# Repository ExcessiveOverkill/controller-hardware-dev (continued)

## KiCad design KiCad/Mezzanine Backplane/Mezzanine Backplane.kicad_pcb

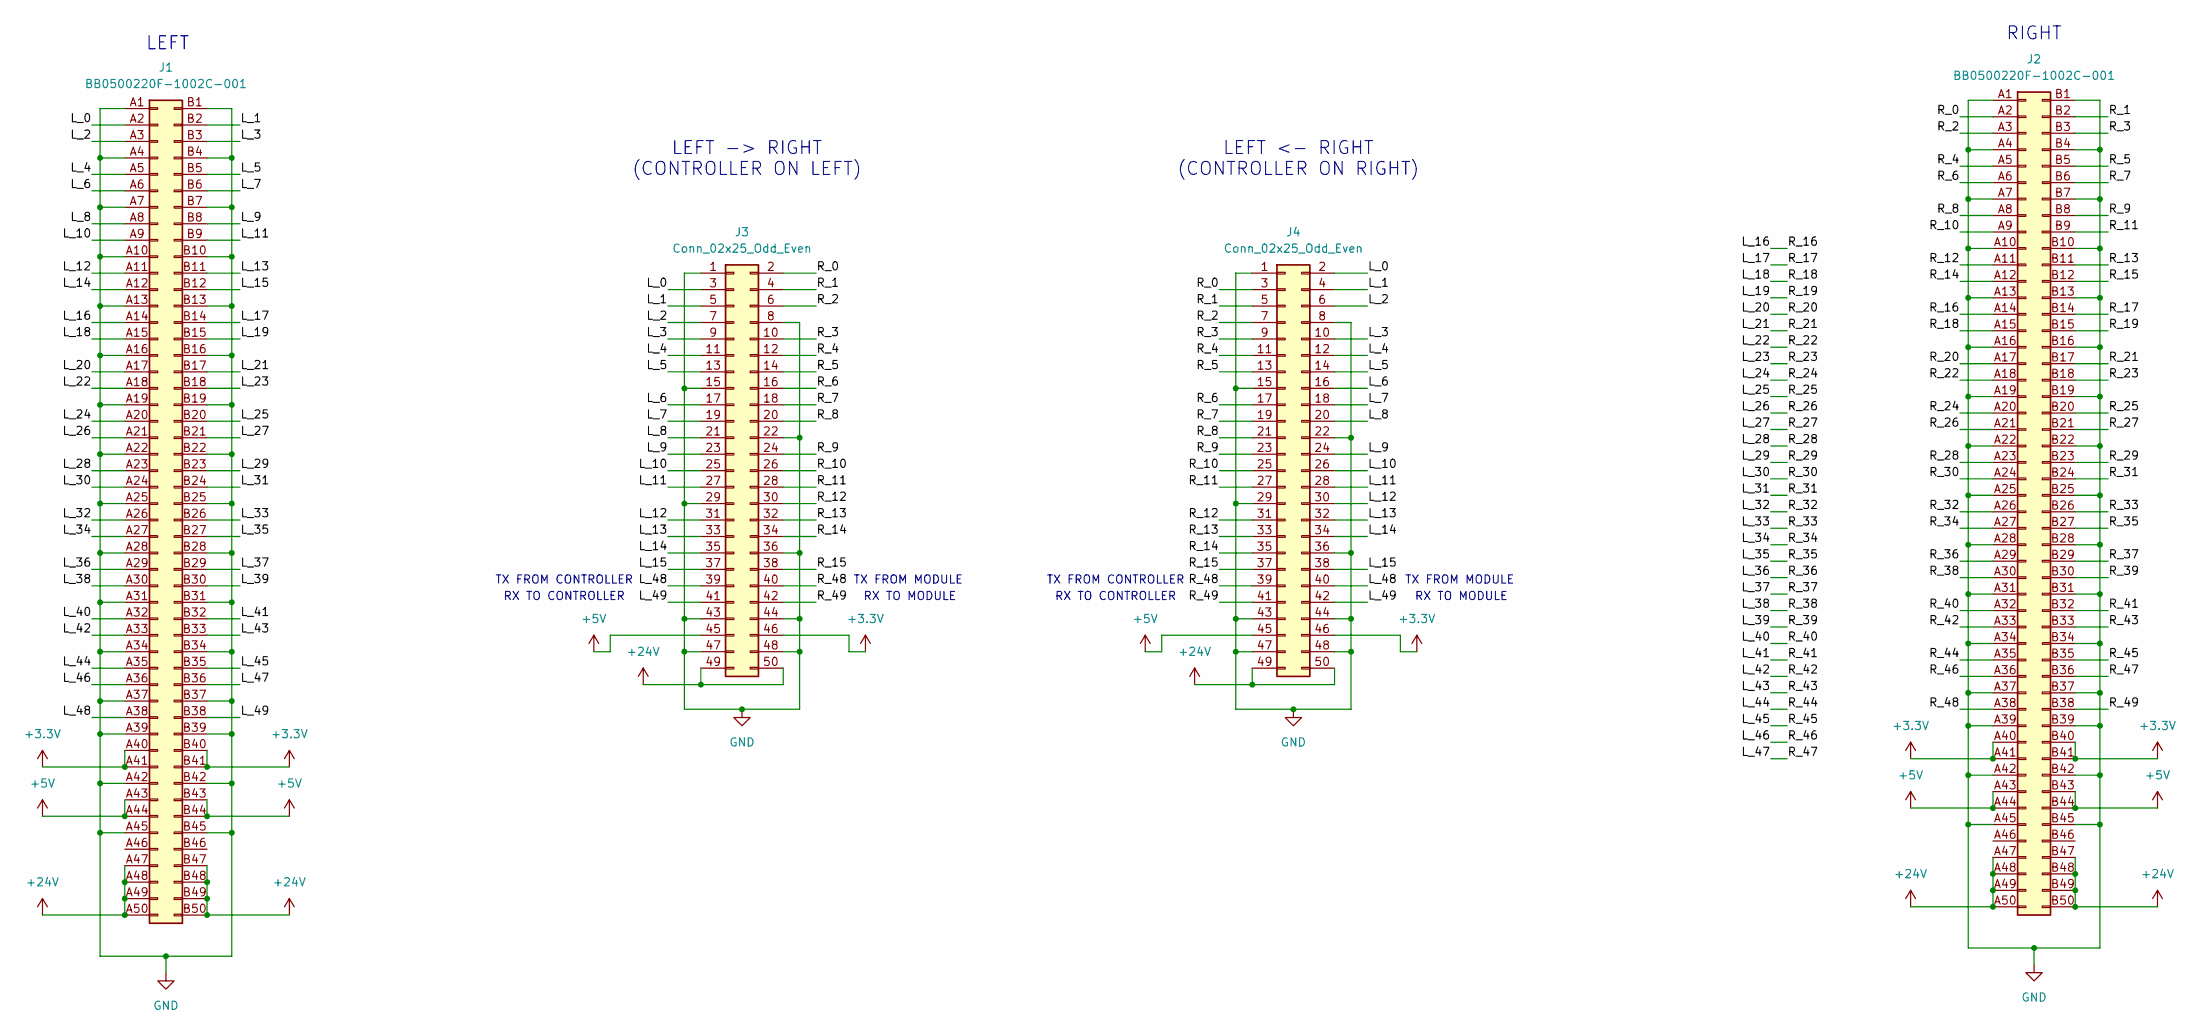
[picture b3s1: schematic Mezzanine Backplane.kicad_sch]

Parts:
J1, J2: BB0500220F-1002C-001; Part Number BB0500220F-1002C-001; LCSC# C42421167
J3, J4: Conn_02x25_Odd_Even; PinSocket_2x25_P2.00mm_Vertical_SMD; Part Number HC-PM200-4.3H-2x25PS; LCSC# C42163108

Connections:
+3.3V: J1.A40, J1.A41, J1.B40, J1.B41, J2.A40, J2.A41, J2.B40, J2.B41, J3.46, J4.46
+5V: J1.A43, J1.A44, J1.B43, J1.B44, J2.A43, J2.A44, J2.B43, J2.B44, J3.45, J4.45
+24V: J1.A47, J1.A48, J1.A49, J1.A50, J1.B47, J1.B48, J1.B49, J1.B50, J2.A47, J2.A48, J2.A49, J2.A50, J2.B47, J2.B48, J2.B49, J2.B50, J3.49, J3.50, J4.49, J4.50
/L_0: J1.A2, J3.3, J4.2
/L_1: J1.B2, J3.5, J4.4
/L_2: J1.A3, J3.7, J4.6
/L_3: J1.B3, J3.9, J4.10
/L_4: J1.A5, J3.11, J4.12
/L_5: J1.B5, J3.13, J4.14
/L_6: J1.A6, J3.17, J4.16
/L_7: J1.B6, J3.19, J4.18
/L_8: J1.A8, J3.21, J4.20
/L_9: J1.B8, J3.23, J4.24
/L_10: J1.A9, J3.25, J4.26
/L_11: J1.B9, J3.27, J4.28
/L_12: J1.A11, J3.31, J4.30
/L_13: J1.B11, J3.33, J4.32
/L_14: J1.A12, J3.35, J4.34
/L_15: J1.B12, J3.37, J4.38
/L_16: J1.A14, J2.A14
/L_17: J1.B14, J2.B14
/L_18: J1.A15, J2.A15
/L_19: J1.B15, J2.B15
/L_20: J1.A17, J2.A17
/L_21: J1.B17, J2.B17
/L_22: J1.A18, J2.A18
/L_23: J1.B18, J2.B18
/L_24: J1.A20, J2.A20
/L_25: J1.B20, J2.B20
/L_26: J1.A21, J2.A21
/L_27: J1.B21, J2.B21
/L_28: J1.A23, J2.A23
/L_29: J1.B23, J2.B23
/L_30: J1.A24, J2.A24
/L_31: J1.B24, J2.B24
/L_32: J1.A26, J2.A26
/L_33: J1.B26, J2.B26
/L_34: J1.A27, J2.A27
/L_35: J1.B27, J2.B27
/L_36: J1.A29, J2.A29
/L_37: J1.B29, J2.B29
/L_38: J1.A30, J2.A30
/L_39: J1.B30, J2.B30
/L_40: J1.A32, J2.A32
/L_41: J1.B32, J2.B32
/L_42: J1.A33, J2.A33
/L_43: J1.B33, J2.B33
/L_44: J1.A35, J2.A35
/L_45: J1.B35, J2.B35
/L_46: J1.A36, J2.A36
/L_47: J1.B36, J2.B36
/L_48: J1.A38, J3.39, J4.40
/L_49: J1.B38, J3.41, J4.42
/R_0: J2.A2, J3.2, J4.3
/R_1: J2.B2, J3.4, J4.5
/R_2: J2.A3, J3.6, J4.7
/R_3: J2.B3, J3.10, J4.9
/R_4: J2.A5, J3.12, J4.11
/R_5: J2.B5, J3.14, J4.13
/R_6: J2.A6, J3.16, J4.17
/R_7: J2.B6, J3.18, J4.19
/R_8: J2.A8, J3.20, J4.21
/R_9: J2.B8, J3.24, J4.23
/R_10: J2.A9, J3.26, J4.25
/R_11: J2.B9, J3.28, J4.27
/R_12: J2.A11, J3.30, J4.31
/R_13: J2.B11, J3.32, J4.33
/R_14: J2.A12, J3.34, J4.35
/R_15: J2.B12, J3.38, J4.37
/R_48: J2.A38, J3.40, J4.39
/R_49: J2.B38, J3.42, J4.41
GND: J1.A1, J1.A4, J1.A7, J1.A10, J1.A13, J1.A16, J1.A19, J1.A22, J1.A25, J1.A28, J1.A31, J1.A34, J1.A37, J1.A39, J1.A42, J1.A45, J1.B1, J1.B4, J1.B7, J1.B10, J1.B13, J1.B16, J1.B19, J1.B22, J1.B25, J1.B28, J1.B31, J1.B34, J1.B37, J1.B39, J1.B42, J1.B45, J2.A1, J2.A4, J2.A7, J2.A10, J2.A13, J2.A16, J2.A19, J2.A22, J2.A25, J2.A28, J2.A31, J2.A34, J2.A37, J2.A39, J2.A42, J2.A45, J2.B1, J2.B4, J2.B7, J2.B10, J2.B13, J2.B16, J2.B19, J2.B22, J2.B25, J2.B28, J2.B31, J2.B34, J2.B37, J2.B39, J2.B42, J2.B45, J3.1, J3.8, J3.15, J3.22, J3.29, J3.36, J3.43, J3.44, J3.47, J3.48, J4.1, J4.8, J4.15, J4.22, J4.29, J4.36, J4.43, J4.44, J4.47, J4.48

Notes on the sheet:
RX TO MODULE
TX FROM MODULE
RIGHT
LEFT
LEFT <- RIGHT (CONTROLLER ON RIGHT)
RX TO CONTROLLER
TX FROM CONTROLLER
LEFT -> RIGHT (CONTROLLER ON LEFT)

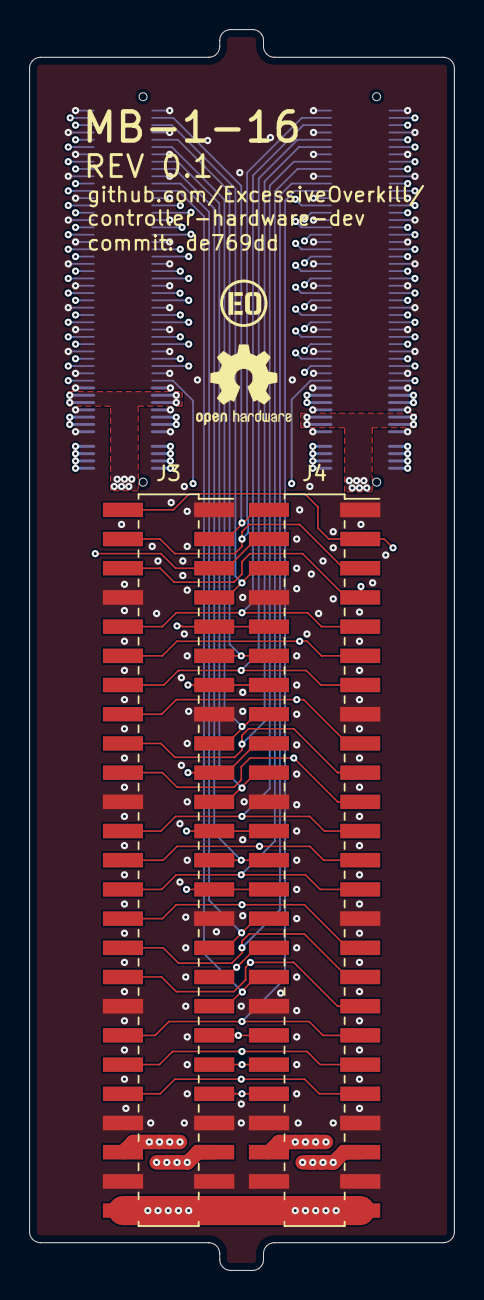
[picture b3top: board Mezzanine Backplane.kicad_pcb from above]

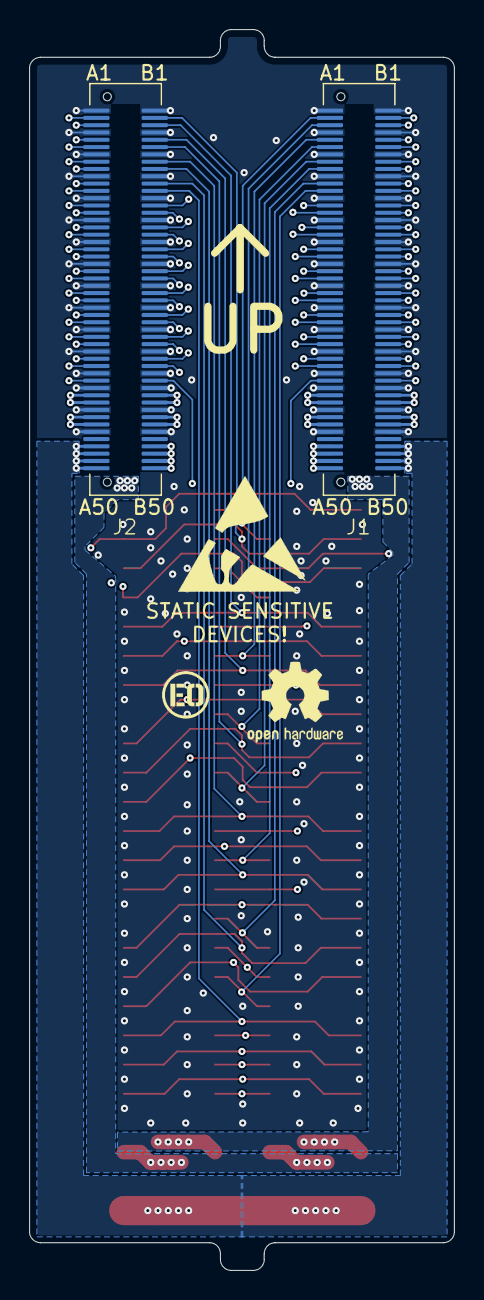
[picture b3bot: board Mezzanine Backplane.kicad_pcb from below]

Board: 4 copper layers, 29.1 x 85.0 mm, 4 parts (2 on the bottom side), 72 nets.

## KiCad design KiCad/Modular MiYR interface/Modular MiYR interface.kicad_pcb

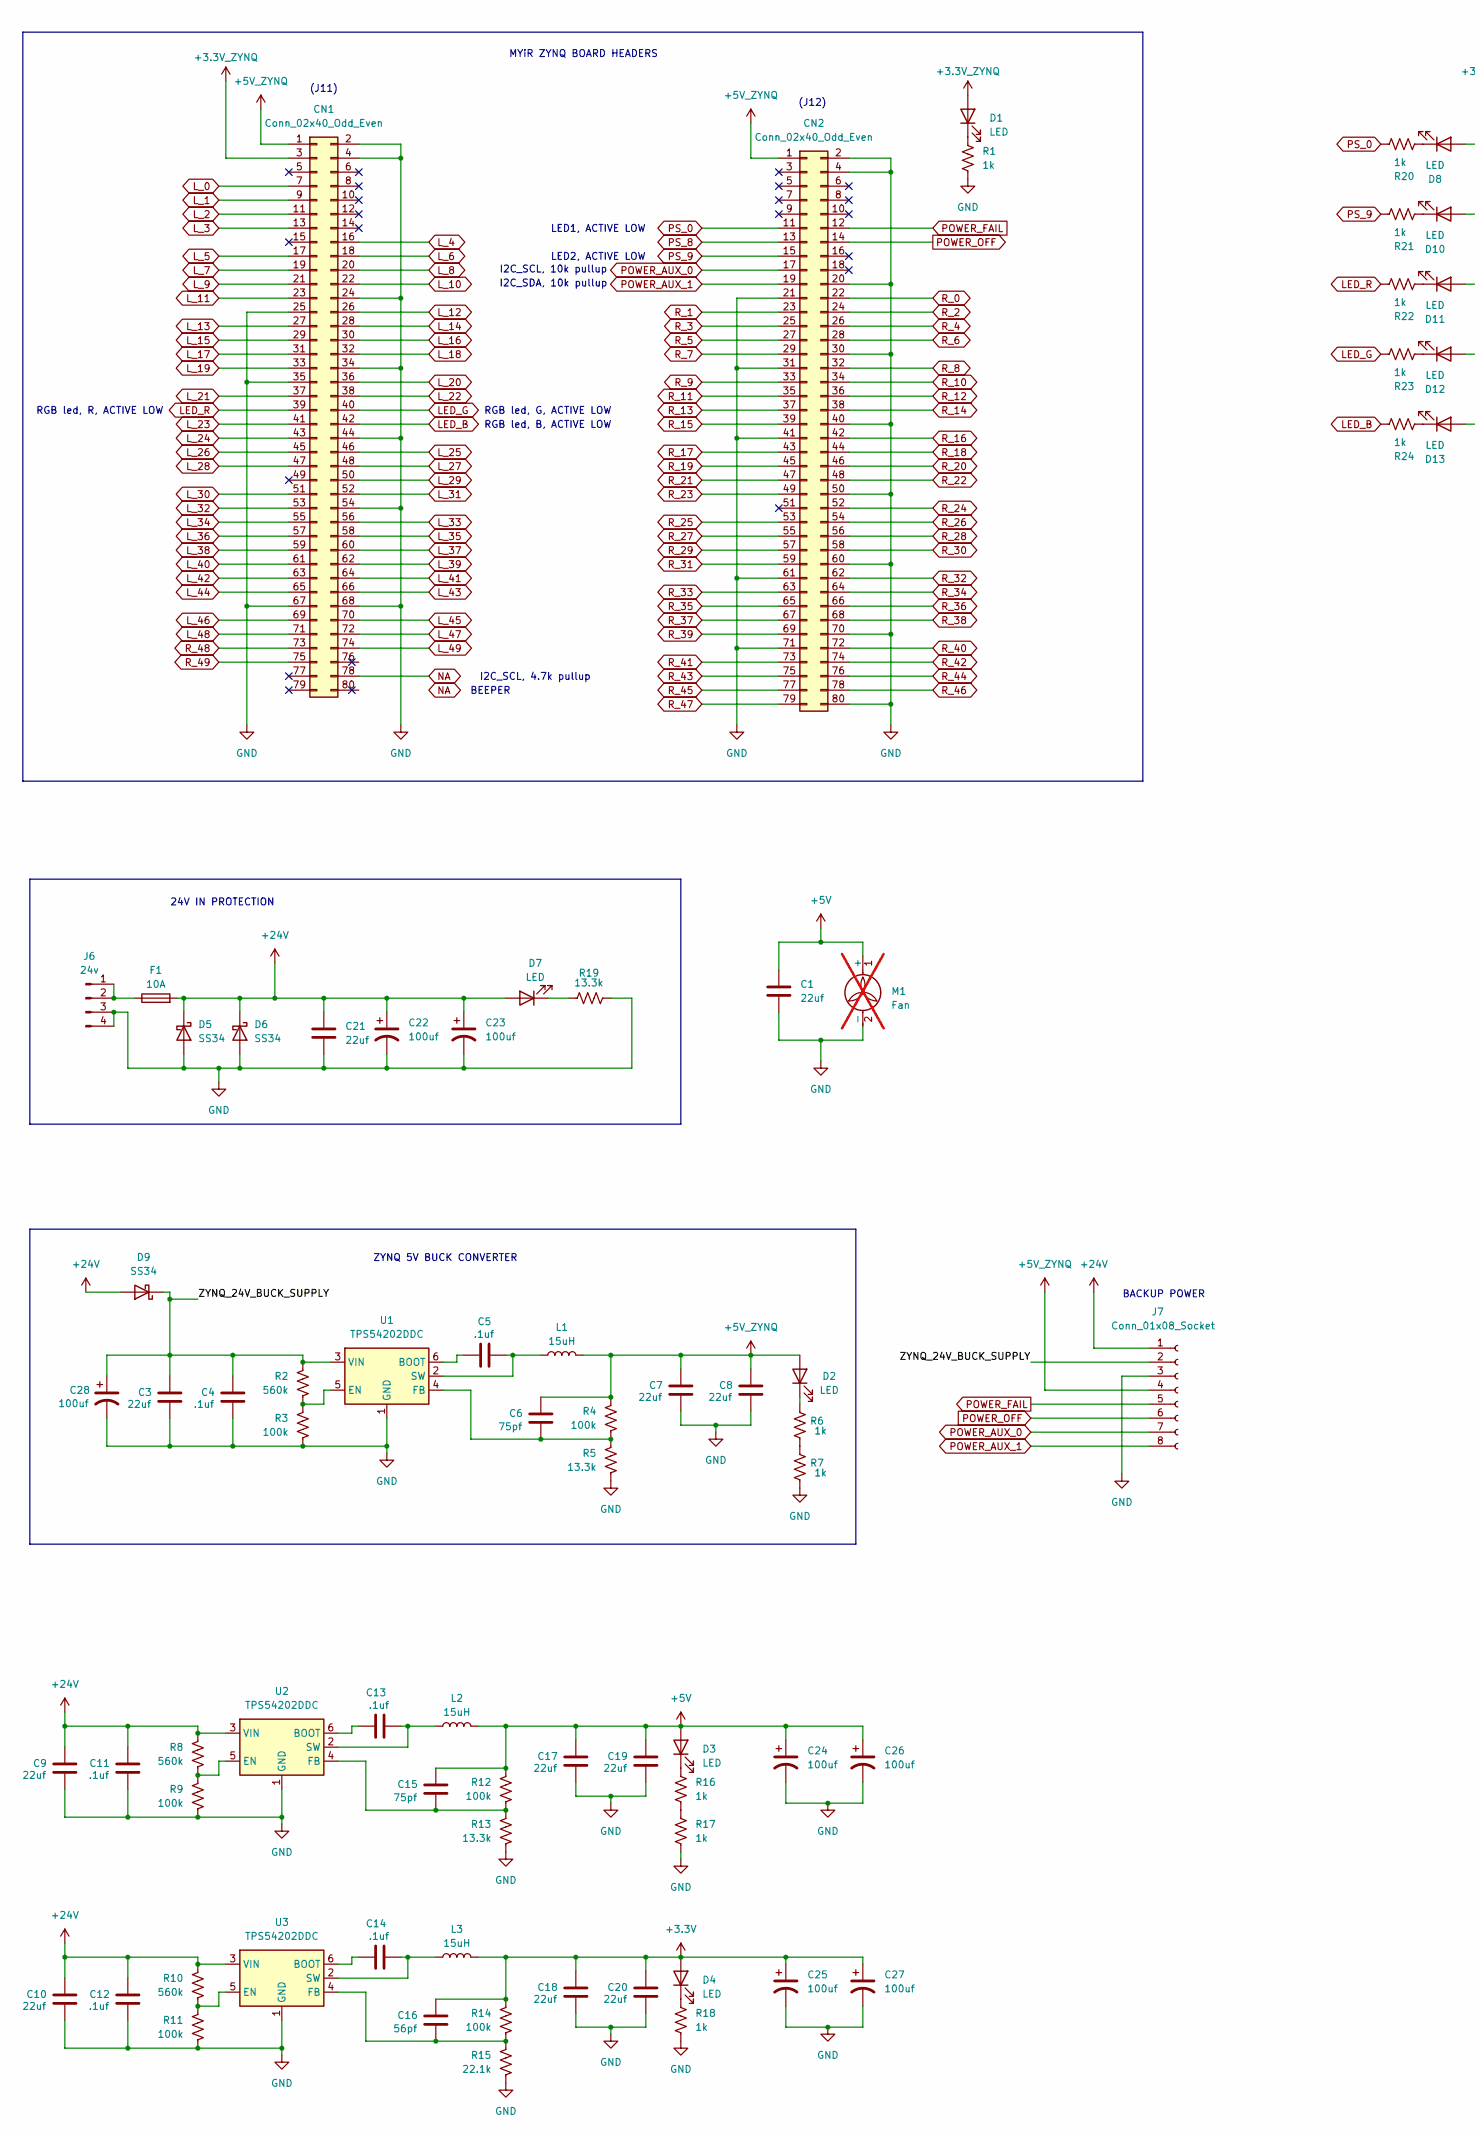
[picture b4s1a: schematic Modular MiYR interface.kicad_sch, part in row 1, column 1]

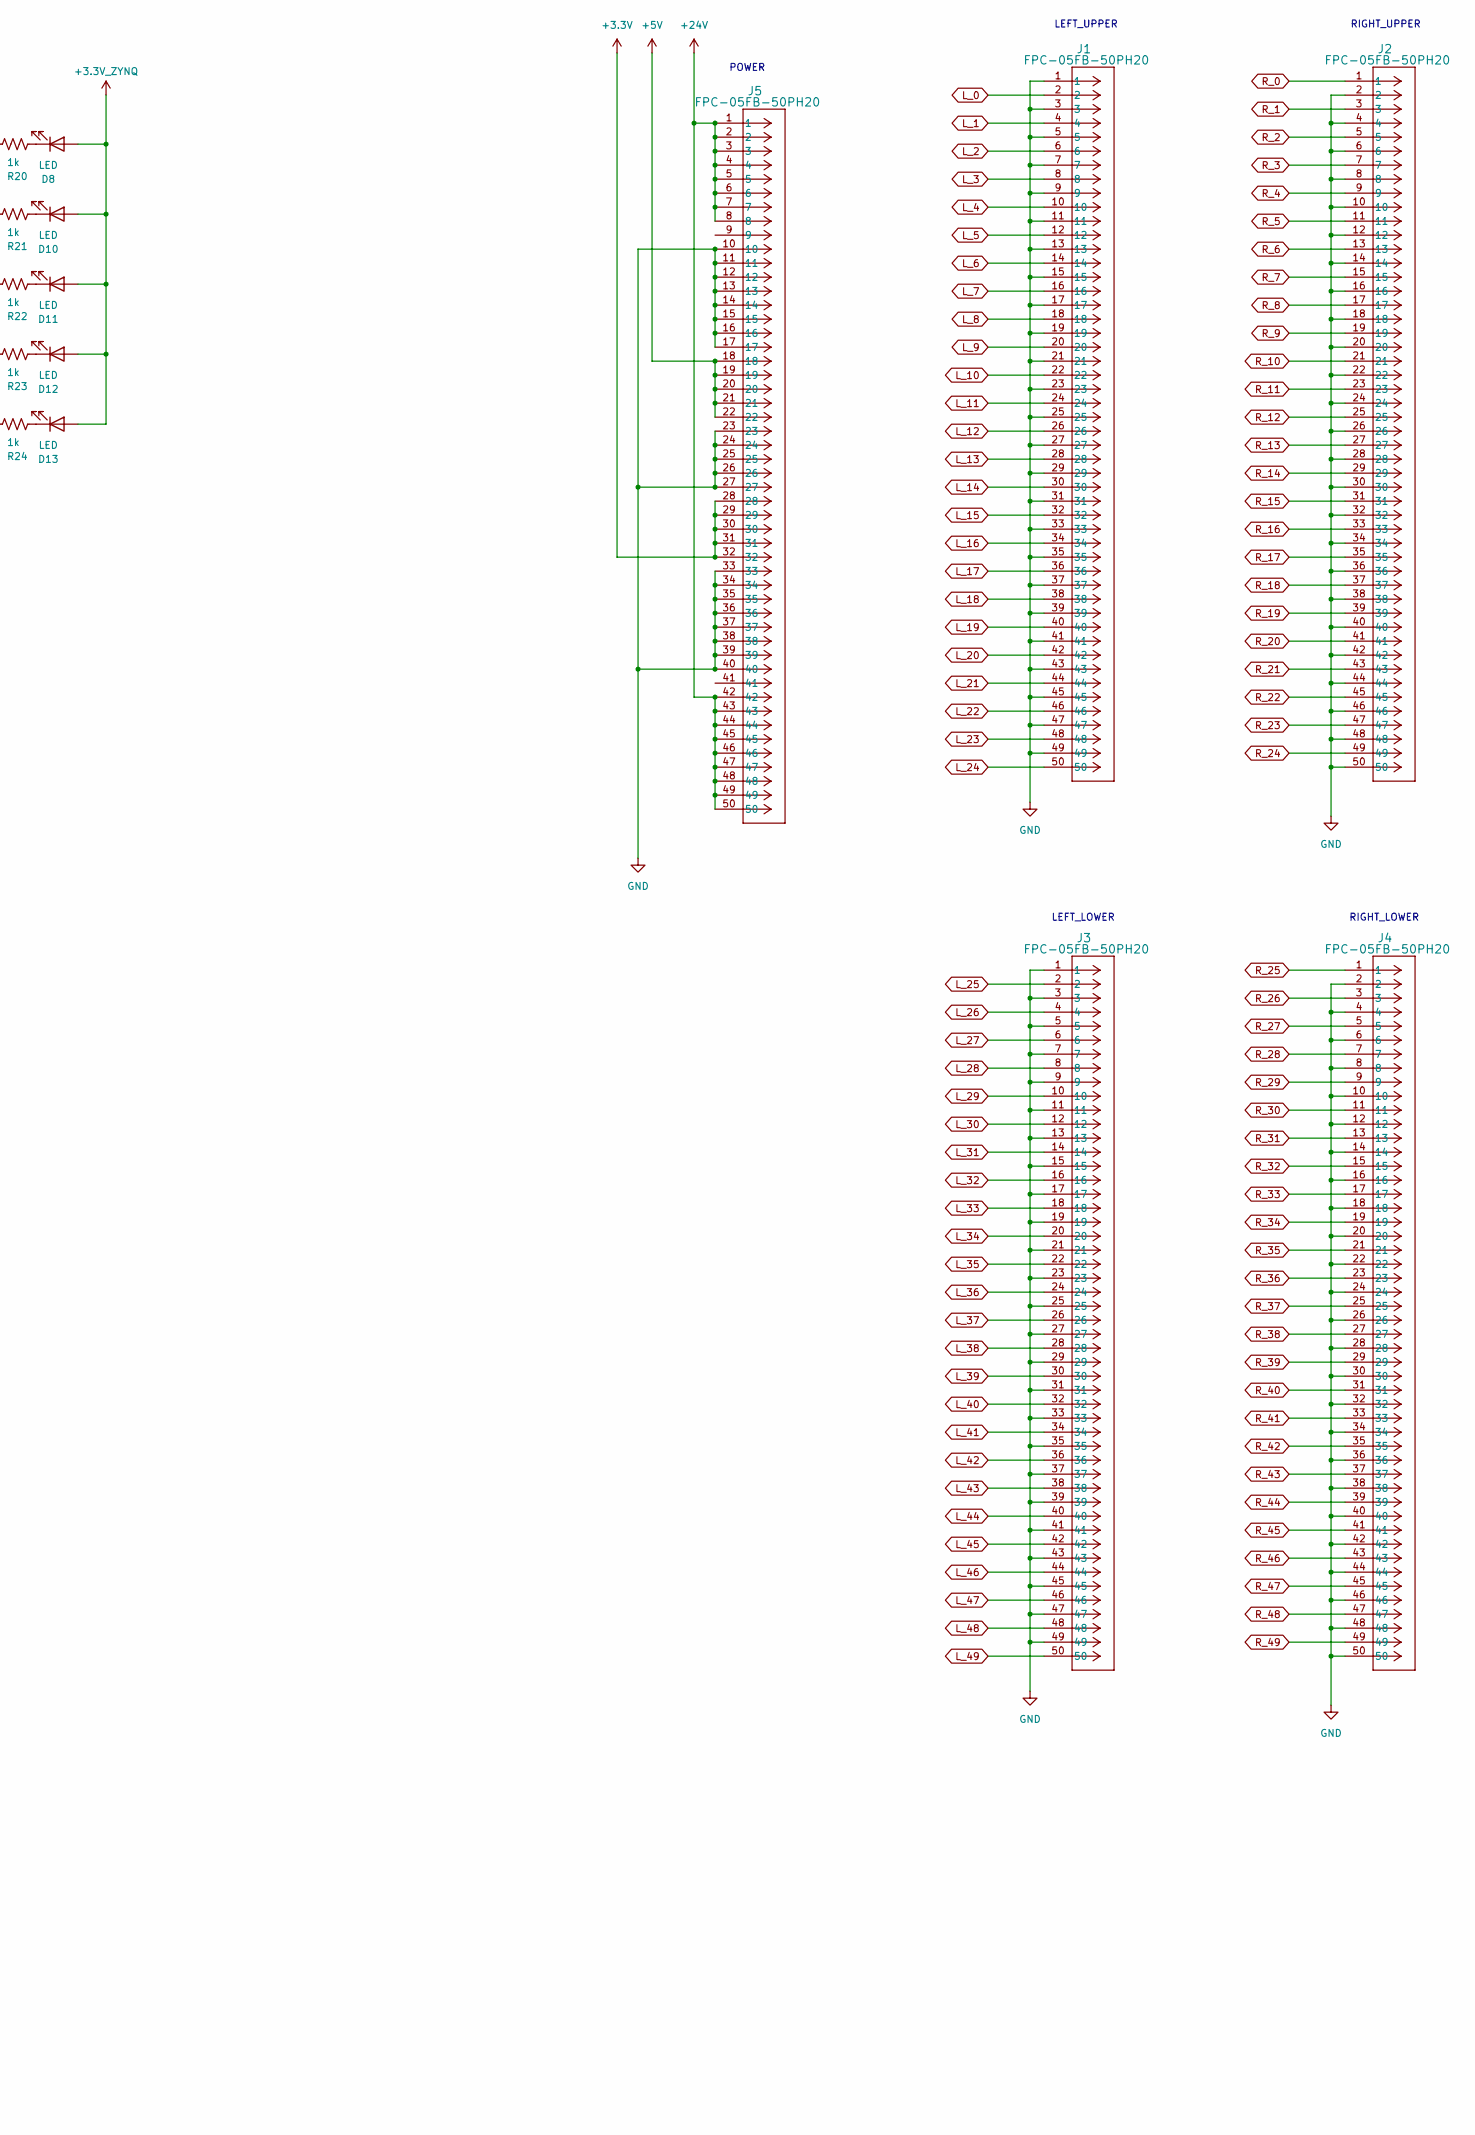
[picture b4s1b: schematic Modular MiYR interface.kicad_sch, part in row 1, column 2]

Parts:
C1, C3, C7, C8, C9, C10, C17, C18, C19, C20, C21: 22uf; C_1206_3216Metric; Part Number CL31A226KAHNNNE; LCSC# C12891
C4, C5, C11, C12, C13, C14: .1uf; C_0402_1005Metric; Part Number CC0402KRX5R9BB104; LCSC# C105882
C6, C15: 75pf; C_0402_1005Metric; Part Number CC0402JRNPO9BN750; LCSC# C107010
C16: 56pf; C_0402_1005Metric; Part Number CC0402JRNPO9BN560; LCSC# C107007
C22, C23, C24, C25, C26, C27, C28: 100uf; CP_Elec_6.3x7.7; Part Number RVT1V101M0607; LCSC# C72478
CN1, CN2: Conn_02x40_Odd_Even; PinHeader_2x40_P1.27mm_Vertical_SMD_FLIPPED; Part Number HDGC127-PS2-40; LCSC# C45359092
D1, D2, D3, D4, D7, D8, D10, D11, D12, D13: LED; LED_0603_1608Metric; Part Number XL-1608UBC-04; LCSC# C965807
D5, D6, D9: SS34; D_SMA; Part Number SS34; LCSC# C8678
F1: 10A; Fuse_1206_3216Metric; Part Number JFC1206-2100FS; LCSC# C136354
J1, J2, J3, J4, J5: FPC-05FB-50PH20; CONN50_FPC-05FB-50PH20_XNP
J6: 24v; 2x02_P3.5_KF2EDGSR
J7: Conn_01x08_Socket; PinHeader_1x08_P2.54mm_Vertical
L1, L2, L3: 15uH; CY54_INDUCTOR; Part Number CY54-15UH; LCSC# C2929432
M1: Fan; PinHeader_1x02_P2.54mm_Vertical; not fitted
R1, R6, R7, R16, R17, R18, R20, R21, R22, R23, R24: 1k; R_0402_1005Metric; Part Number RC0402FR-071KL; LCSC# C106235
R2, R8, R10: 560k; R_0402_1005Metric; Part Number RC0402FR-07560KL; LCSC# C137958
R3, R4, R9, R11, R12, R14: 100k; R_0402_1005Metric; Part Number RC0402FR-07100KL; LCSC# C60491
R5, R13, R19: 13.3k; R_0402_1005Metric; Part Number RC0402FR-0713K3L; LCSC# C274352
R15: 22.1k; R_0402_1005Metric; Part Number RC0402FR-0722K1L; LCSC# C163478
U1, U2, U3: TPS54202DDC; SOT-23-6; Part Number TPS54202DDCR; LCSC# C191884

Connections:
+3.3V: C16.2, C18.2, C20.2, C25.1, C27.1, D4.2 (A), J5.28, J5.29, J5.30, J5.31, J5.32, L3.2, R14.2
+3.3V_ZYNQ: CN1.3, D1.2 (A), D8.2 (A), D10.2 (A), D11.2 (A), D12.2 (A), D13.2 (A)
+5V: C1.1, C15.2, C17.2, C19.2, C24.1, C26.1, D3.2 (A), J5.18, J5.19, J5.20, J5.21, J5.22, L2.2, M1.1 (+), R12.2
+5V_ZYNQ: C6.2, C7.2, C8.2, CN1.1, CN2.1, D2.2 (A), J7.4, L1.2, R4.2
+24V: C9.2, C10.2, C11.2, C12.2, C21.1, C22.1, C23.1, D5.1 (K), D6.1 (K), D7.2 (A), D9.2 (A), F1.2, J5.1, J5.2, J5.3, J5.4, J5.5, J5.6, J5.7, J5.8, J5.42, J5.43, J5.44, J5.45, J5.46, J5.47, J5.48, J5.49, J5.50, J7.1, R8.2, R10.2, U2.3 (VIN), U3.3 (VIN)
/ZYNQ_24V_BUCK_SUPPLY: C3.2, C4.2, C28.1, D9.1 (K), J7.2, R2.2, U1.3 (VIN)
GND: C1.2, C3.1, C4.1, C7.1, C8.1, C9.1, C10.1, C11.1, C12.1, C17.1, C18.1, C19.1, C20.1, C21.2, C22.2, C23.2, C24.2, C25.2, C26.2, C27.2, C28.2, CN1.2, CN1.4, CN1.24, CN1.25, CN1.34, CN1.35, CN1.44, CN1.54, CN1.67, CN1.68, CN2.2, CN2.4, CN2.20, CN2.21, CN2.30, CN2.31, CN2.40, CN2.41, CN2.50, CN2.60, CN2.61, CN2.70, CN2.71, CN2.80, D5.2 (A), D6.2 (A), J1.1, J1.3, J1.5, J1.7, J1.9, J1.11, J1.13, J1.15, J1.17, J1.19, J1.21, J1.23, J1.25, J1.27, J1.29, J1.31, J1.33, J1.35, J1.37, J1.39, J1.41, J1.43, J1.45, J1.47, J1.49, J2.2, J2.4, J2.6, J2.8, J2.10, J2.12, J2.14, J2.16, J2.18, J2.20, J2.22, J2.24, J2.26, J2.28, J2.30, J2.32, J2.34, J2.36, J2.38, J2.40, J2.42, J2.44, J2.46, J2.48, J2.50, J3.1, J3.3, J3.5, J3.7, J3.9, J3.11, J3.13, J3.15, J3.17, J3.19, J3.21, J3.23, J3.25, J3.27, J3.29, J3.31, J3.33, J3.35, J3.37, J3.39, J3.41, J3.43, J3.45, J3.47, J3.49, J4.2, J4.4, J4.6, J4.8, J4.10, J4.12, J4.14, J4.16, J4.18, J4.20, J4.22, J4.24, J4.26, J4.28, J4.30, J4.32, J4.34, J4.36, J4.38, J4.40, J4.42, J4.44, J4.46, J4.48, J4.50, J5.10, J5.11, J5.12, J5.13, J5.14, J5.15, J5.16, J5.17, J5.23, J5.24, J5.25, J5.26, J5.27, J5.33, J5.34, J5.35, J5.36, J5.37, J5.38, J5.39, J5.40, J6.3, J6.4, J7.3, M1.2 (-), R1.1, R3.1, R5.1, R7.1, R9.1, R11.1, R13.1, R15.1, R17.1, R18.1, R19.1, U1.1 (GND), U2.1 (GND), U3.1 (GND)
LED_B: CN1.42, R24.1
LED_G: CN1.40, R23.1
LED_R: CN1.39, R22.1
L_0: CN1.7, J1.2
L_1: CN1.9, J1.4
L_2: CN1.11, J1.6
L_3: CN1.13, J1.8
L_4: CN1.16, J1.10
L_5: CN1.17, J1.12
L_6: CN1.18, J1.14
L_7: CN1.19, J1.16
L_8: CN1.20, J1.18
L_9: CN1.21, J1.20
L_10: CN1.22, J1.22
L_11: CN1.23, J1.24
L_12: CN1.26, J1.26
L_13: CN1.27, J1.28
L_14: CN1.28, J1.30
L_15: CN1.29, J1.32
L_16: CN1.30, J1.34
L_17: CN1.31, J1.36
L_18: CN1.32, J1.38
L_19: CN1.33, J1.40
L_20: CN1.36, J1.42
L_21: CN1.37, J1.44
L_22: CN1.38, J1.46
L_23: CN1.41, J1.48
L_24: CN1.43, J1.50
L_25: CN1.46, J3.2
L_26: CN1.45, J3.4
L_27: CN1.48, J3.6
L_28: CN1.47, J3.8
L_29: CN1.50, J3.10
L_30: CN1.51, J3.12
L_31: CN1.52, J3.14
L_32: CN1.53, J3.16
L_33: CN1.56, J3.18
L_34: CN1.55, J3.20
L_35: CN1.58, J3.22
L_36: CN1.57, J3.24
L_37: CN1.60, J3.26
L_38: CN1.59, J3.28
L_39: CN1.62, J3.30
L_40: CN1.61, J3.32
L_41: CN1.64, J3.34
L_42: CN1.63, J3.36
L_43: CN1.66, J3.38
L_44: CN1.65, J3.40
L_45: CN1.70, J3.42
L_46: CN1.69, J3.44
L_47: CN1.72, J3.46
L_48: CN1.71, J3.48
L_49: CN1.74, J3.50
NA: CN1.78
unnamed: D1.1 (K), R1.2
unnamed: D2.1 (K), R6.2
unnamed: D3.1 (K), R16.2
unnamed: D4.1 (K), R18.2
unnamed: D7.1 (K), R19.2
unnamed: D8.1 (K), R20.2
unnamed: D10.1 (K), R21.2
unnamed: D11.1 (K), R22.2
unnamed: D12.1 (K), R23.2
unnamed: D13.1 (K), R24.2
unnamed: F1.1, J6.1, J6.2
unnamed: R6.1, R7.2
unnamed: R16.1, R17.2
unnamed: C5.1, U1.6 (BOOT)
unnamed: R2.1, R3.2, U1.5 (EN)
unnamed: C6.1, R4.1, R5.2, U1.4 (FB)
unnamed: C5.2, L1.1, U1.2 (SW)
unnamed: C13.1, U2.6 (BOOT)
unnamed: R8.1, R9.2, U2.5 (EN)
unnamed: C15.1, R12.1, R13.2, U2.4 (FB)
unnamed: C13.2, L2.1, U2.2 (SW)
unnamed: C14.1, U3.6 (BOOT)
unnamed: R10.1, R11.2, U3.5 (EN)
unnamed: C16.1, R14.1, R15.2, U3.4 (FB)
unnamed: C14.2, L3.1, U3.2 (SW)
POWER_AUX_0: CN2.17, J7.7
POWER_AUX_1: CN2.19, J7.8
POWER_FAIL: CN2.12, J7.5
POWER_OFF: CN2.14, J7.6
PS_0: CN2.11, R20.1
PS_8: CN2.13
PS_9: CN2.15, R21.1
R_0: CN2.22, J2.1
R_1: CN2.23, J2.3
R_2: CN2.24, J2.5
R_3: CN2.25, J2.7
R_4: CN2.26, J2.9
R_5: CN2.27, J2.11
R_6: CN2.28, J2.13
R_7: CN2.29, J2.15
R_8: CN2.32, J2.17
R_9: CN2.33, J2.19
R_10: CN2.34, J2.21
R_11: CN2.35, J2.23
R_12: CN2.36, J2.25
R_13: CN2.37, J2.27
R_14: CN2.38, J2.29
R_15: CN2.39, J2.31
R_16: CN2.42, J2.33
R_17: CN2.43, J2.35
R_18: CN2.44, J2.37
R_19: CN2.45, J2.39
R_20: CN2.46, J2.41
R_21: CN2.47, J2.43
R_22: CN2.48, J2.45
R_23: CN2.49, J2.47
R_24: CN2.52, J2.49
R_25: CN2.53, J4.1
R_26: CN2.54, J4.3
R_27: CN2.55, J4.5
R_28: CN2.56, J4.7
R_29: CN2.57, J4.9
R_30: CN2.58, J4.11
R_31: CN2.59, J4.13
R_32: CN2.62, J4.15
R_33: CN2.63, J4.17
R_34: CN2.64, J4.19
R_35: CN2.65, J4.21
R_36: CN2.66, J4.23
R_37: CN2.67, J4.25
R_38: CN2.68, J4.27
R_39: CN2.69, J4.29
R_40: CN2.72, J4.31
R_41: CN2.73, J4.33
R_42: CN2.74, J4.35
R_43: CN2.75, J4.37
R_44: CN2.76, J4.39
R_45: CN2.77, J4.41
R_46: CN2.78, J4.43
R_47: CN2.79, J4.45
R_48: CN1.73, J4.47
R_49: CN1.75, J4.49

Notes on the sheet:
RIGHT_LOWER
MYiR ZYNQ BOARD HEADERS
BEEPER
24V IN PROTECTION
RGB led, B, ACTIVE LOW
POWER
ZYNQ 5V BUCK CONVERTER
RIGHT_UPPER
I2C_SCL, 10k pullup
RGB led, G, ACTIVE LOW
LED1, ACTIVE LOW
I2C_SDA, 10k pullup
LEFT_LOWER
(J11)
LED2, ACTIVE LOW
LEFT_UPPER
BACKUP POWER
I2C_SCL, 4.7k pullup
(J12)
RGB led, R, ACTIVE LOW

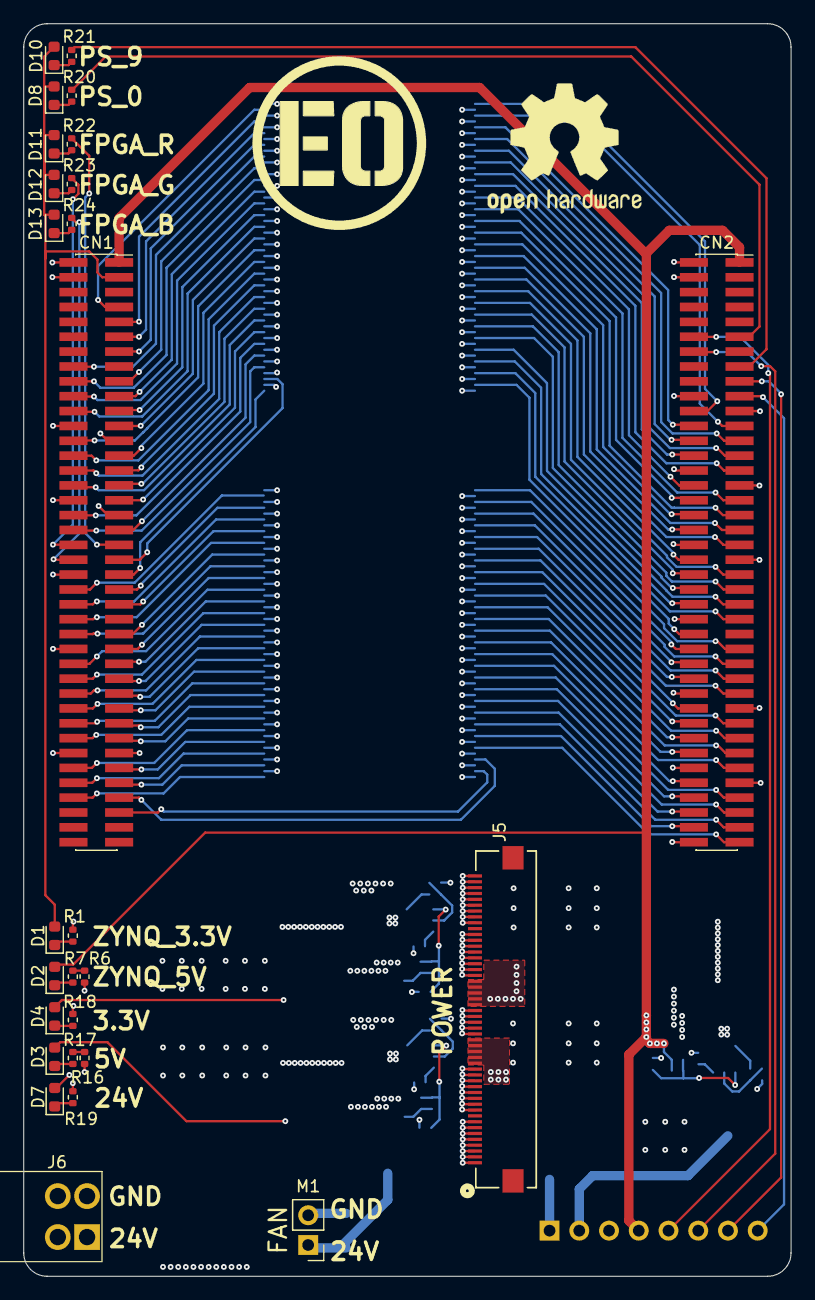
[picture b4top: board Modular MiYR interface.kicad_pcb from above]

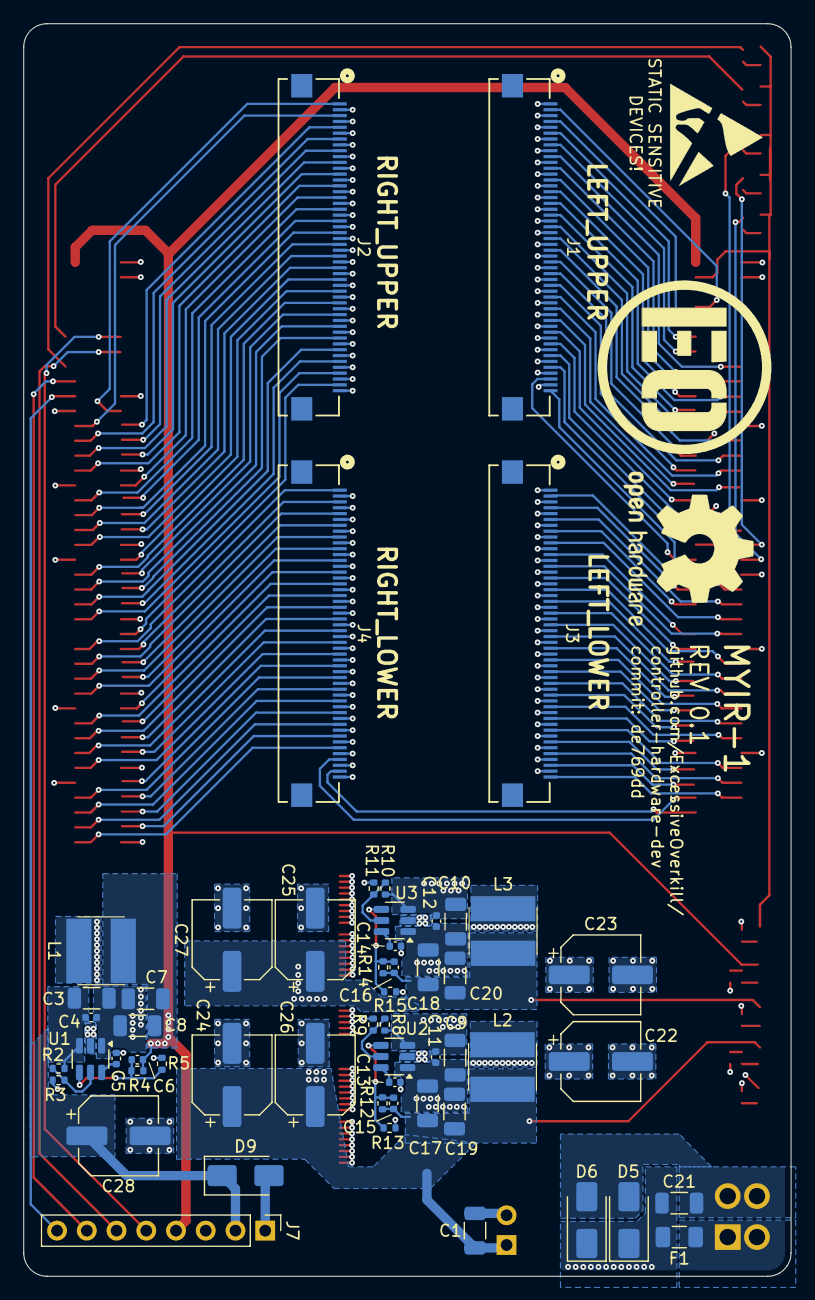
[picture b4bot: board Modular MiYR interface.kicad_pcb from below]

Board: 4 copper layers, 65.5 x 107.0 mm, 81 parts (54 on the bottom side), 141 nets.

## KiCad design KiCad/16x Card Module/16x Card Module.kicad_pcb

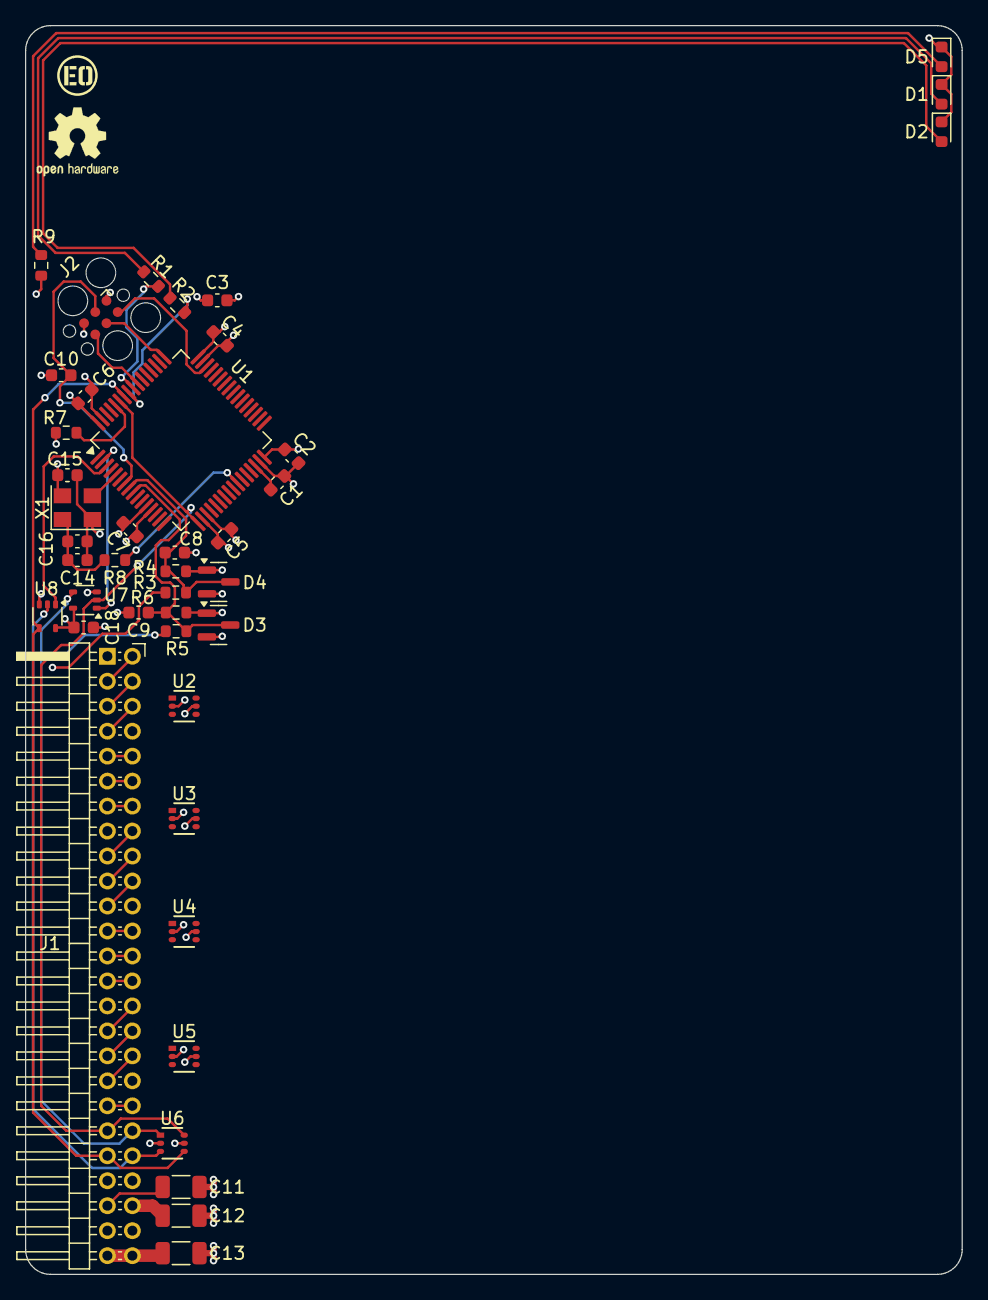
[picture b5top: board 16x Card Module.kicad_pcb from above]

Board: 4 copper layers, 75.0 x 100.0 mm, 42 parts (0 on the bottom side), 42 nets.

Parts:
C1, C3: 4.7uf; C_0603_1608Metric
C2, C4, C5, C6, C7, C8, C9, C10, C15, C16, C18: .1uf; C_0603_1608Metric
C11, C12, C13: 22uf; C_1206_3216Metric
C14: 2.2uf; C_0603_1608Metric
D1, D2, D5: LED; LED_0603_1608Metric
D3, D4: BAT54SLT1G; SOT-23
J1: Conn_02x25_Odd_Even; 16x_modular_card
J2: Conn_ARM_SWD_TagConnect_TC2030; Tag-Connect_TC2030-IDC-FP_2x03_P1.27mm_Vertical
R1, R2, R6, R8, R9: 1k; R_0603_1608Metric
R3, R4, R5, R7: 10k; R_0603_1608Metric
U1: STM32F411RETx; LQFP-64_10x10mm_P0.5mm
U2, U3, U4, U5, U6: D1213A-04S-7; SOT-363_DIO
U7, U8: 74LVC1G126; SOT-353_SC-70-5
X1: 16Mhz; Oscillator_SMD_SeikoEpson_SG8002CE-4Pin_3.2x2.5mm

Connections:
+3.3V: C2.1, C3.1, C4.1, C5.1, C6.1, C7.1, C12.2, C15.2, C18.2, D3.2 (K), D4.2 (K), J1.46, J2.1 (VCC), R9.1, U1.13 (VDDA), U1.19 (VDD), U1.32 (VDD), U1.48 (VDD), U1.64 (VDD), U2.5 (VCC), U3.5 (VCC), U4.5 (VCC), U5.5 (VCC), U6.5 (VCC), U7.5 (VCC), U8.5 (VCC), X1.4 (Vcc)
+5V: C11.2, J1.45, R3.1
+24V: C13.2, J1.49, J1.50, R5.1
/FPGA Connector/IN_0: J1.2, J1.3
/FPGA Connector/IN_1: J1.4, J1.5
/FPGA Connector/IN_2: J1.6, J1.7
/FPGA Connector/IN_3: J1.9, J1.10
/FPGA Connector/IN_4: J1.11, J1.12
/FPGA Connector/IN_5: J1.13, J1.14
/FPGA Connector/IN_6: J1.16, J1.17
/FPGA Connector/IN_7: J1.18, J1.19
/FPGA Connector/IN_8: J1.20, J1.21
/FPGA Connector/IN_9: J1.23, J1.24
/FPGA Connector/IN_10: J1.25, J1.26
/FPGA Connector/IN_11: J1.27, J1.28
/FPGA Connector/IN_12: J1.30, J1.31
/FPGA Connector/IN_13: J1.32, J1.33
/FPGA Connector/IN_14: J1.34, J1.35
/FPGA Connector/IN_15: J1.37, J1.38
/FPGA Connector/MODULE_RX: J1.42, U6.3 (CH2), U8.2
/FPGA Connector/MODULE_TX: J1.40, U6.1 (CH1), U7.4
/MCU/5V_SENSE: C8.1, D4.3 (common), R3.2, R4.1, U1.8 (PC0)
/MCU/24V_SENSE: C9.1, D3.3 (common), R5.2, R6.1, U1.9 (PC1)
/MCU/BOOT_SEL: R7.2, U1.60 (BOOT0)
/MCU/LED_0: R1.1, U1.56 (PB4)
/MCU/LED_1: R2.1, U1.57 (PB5)
/MCU/NRESET: C10.2, J2.3 (~RESET), U1.7 (NRST)
/MCU/OSC: U1.5 (PH0), X1.3 (OUT)
/MCU/RX: J1.39, U1.17 (PA3), U1.59 (PB7), U6.6 (CH4), U7.2
/MCU/RX_PASSTHROUGH_ENABLE: U1.3 (PC14), U8.1
/MCU/SWCLK: J2.4 (SWCLK), U1.49 (PA14)
/MCU/SWDIO: J2.2 (SWDIO), U1.46 (PA13)
/MCU/SWO: J2.6 (SWO), U1.55 (PB3)
/MCU/TX: J1.41, U1.58 (PB6), U6.4 (CH3), U8.4
/MCU/TX_PASSTHROUGH_ENABLE: U1.2 (PC13), U7.1
/MCU/VCXO_TRIM: R8.1, U1.26 (PB0)
GND: C1.2, C2.2, C3.2, C4.2, C5.2, C6.2, C7.2, C8.2, C9.2, C10.1, C11.1, C12.1, C13.1, C14.1, C15.1, C16.1, C18.1, D1.1 (K), D2.1 (K), D3.1 (A), D4.1 (A), D5.1 (K), J1.1, J1.8, J1.15, J1.22, J1.29, J1.36, J1.43, J1.44, J1.47, J1.48, J2.5 (GND), R4.2, R6.2, R7.1, U1.12 (VSSA), U1.18 (VSS), U1.31 (VSS), U1.47 (VSS), U1.63 (VSS), U2.2 (GND), U3.2 (GND), U4.2 (GND), U5.2 (GND), U6.2 (GND), U7.3 (GND), U8.3 (GND), X1.2 (GND)
unnamed: D1.2 (A), R1.2
unnamed: D2.2 (A), R2.2
unnamed: D5.2 (A), R9.2
unnamed: C1.1, U1.30 (VCAP1)
unnamed: C14.2, C16.2, R8.2, X1.1 (OE)
